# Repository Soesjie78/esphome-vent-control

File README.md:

🛠️ Smart Solar-Powered Ventilation Control (Matter / Home Assistant)
Convert your standard home ventilation grill or window register into a smart, energy-independent ventilation system! This 3D-printed project mounts a servo motor to your ventilation control and uses a super energy-efficient ESP32-C6 (FireBeetle 2) to operate automatically via Home Assistant (Matter/Thread or WiFi).

Thanks to advanced deep sleep optimization, this project can run entirely on a small LiPo battery topped up by a tiny solar panel!

## 🚀 Quick Installation

You can flash the firmware directly to your ESP8266 via your browser. Click the button below:

*Note: Please use a browser that supports WebSerial (Chrome, Edge, or Opera).*

✨ Features
Smart Home Integration: Works natively with Home Assistant and Matter via ESPHome.
Extreme Battery Life: The controller stays in ultra-low-power Deep Sleep, waking up every 20 minutes to sync and check for new commands. No massive battery needed!
Zero Latency "Queuing": Uses a Home Assistant Helper (input_select). You can change the desired position at any time in your dashboard; the device picks it up instantly the moment it wakes up.
Smart Memory: The servo only moves if the requested position has actually changed, saving tons of mechanical wear and battery power.
Solar Ready: Designed around the DFRobot FireBeetle 2 form factor for easy solar charging integration.

Further information can be foud at the Makerworld 3D model houding area: https://makerworld.com/en/models/2931636-smart-solar-vent-control-matter-home-assistant#profileId-3281956

## 🔌 Custom PCB (optional)

Prefer a single board instead of a FireBeetle + loose wiring? [`hardware/`](hardware/README.md) contains a
36 × 50 mm KiCad 7 design based on the ESP32-C6-MINI-1. It has a TP4056 solar/USB LiPo charger, a 3.3 V low-Iq LDO,
battery measurement, and a MOSFET that switches the servo supply completely off during deep sleep. Gerbers, BOM and CPL
for JLCPCB assembly are included. Use [`ventcontrol-pcb.yaml`](ventcontrol-pcb.yaml) as the firmware for this board.

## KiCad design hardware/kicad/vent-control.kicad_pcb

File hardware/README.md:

# Vent Control – eigen printplaat (ESP32-C6, zonnepaneel, LiPo, servo)

Een compacte printplaat (**36 × 50 mm, 2 lagen**) die de FireBeetle 2 ESP32-C6 + losse
bedrading vervangt. Alles wat je nu met losse onderdelen doet, zit op de print:
de Schottky-diode voor het zonnepaneel, en de MOSFET + weerstanden die de servo-voeding schakelen.

| Bovenkant | Onderkant (gespiegeld) |
|---|---|
|  |  |

Schema: [production/vent-control-schematic.pdf](production/vent-control-schematic.pdf)

## Wat zit erop

| Blok | Onderdelen | Opmerking |
|---|---|---|
| MCU | **ESP32-C6-MINI-1-N4** (U1) | Thread/Matter, WiFi 6, BLE. PCB-antenne aan de bovenrand; onder de antenne is een kopervrije zone van 5,6 mm. |
| USB-C | J1 + USBLC6-2SC6 (ESD) + 2× 5,1 kΩ CC | Flashen/loggen via de ingebouwde USB-Serial/JTAG (GPIO12/13) en opladen. |
| Zonnepaneel | J3 (JST-PH 2p) + **D2 B5819W Schottky** | USB (D1) en zonnepaneel (D2) zijn via diodes "ge-OR'd" naar de lader. 5–6 V paneel. |
| Lader | **TP4056** (U2), 500 mA (R3 = 2,4 kΩ) | Rode LED = laden, groene LED = vol. Max. ingangsspanning 8 V, dus een 6 V-paneel (Voc ≈ 7 V) is OK. |
| Batterij | J2 (JST-PH 2p), 1S LiPo | **Gebruik een cel mét beveiligingsprintje** (de TP4056 heeft geen onderspanningsbeveiliging). |
| 3,3 V | **XC6220B331MR** LDO (U3) | 1 A, ruststroom ±8 µA, lage dropout. |
| Batterijmeting | 1 MΩ / 1 MΩ + 100 nF → **GPIO0** | Zelfde als de FireBeetle (`multiply: 2.0`). Kost permanent ~2 µA. |
| Servo-voeding | **Q1 AO3401A** (P-FET) + **Q2 2N7002** + R12/R13/R14/C9 | **GPIO2** hoog = servo aan. In deep sleep is de servo volledig spanningsloos. R13/C9 geven een soft-start (~1 ms) tegen inschakelpieken; R14 houdt de servo uit tijdens reset/slaap. 47 µF + 100 nF buffer. |
| Servo | J4 (3-pin header, G-V-S) | Signaal op **GPIO1** via 1 kΩ. Servo (SG90/MG90 360°) draait direct op de accuspanning 3,0–4,2 V. |
| Knoppen/LED | RESET (EN), BOOT (GPIO9), status-LED (**GPIO18**) | GPIO8 heeft de verplichte pull-up voor het opstarten. |

### Pinnen samengevat

| Functie | GPIO | Verschil met FireBeetle-versie |
|---|---|---|
| Servo signaal | GPIO1 | zelfde |
| Batterijspanning (ADC, ×2) | GPIO0 | zelfde |
| Servo voeding aan/uit | GPIO2 | **nieuw** |
| Status-LED | GPIO18 | was GPIO15 ("Battery Measure Enable", dat was in feite de LED) |
| USB D-/D+ | GPIO12/13 | intern |

## Firmware

Gebruik [`../ventcontrol-pcb.yaml`](../ventcontrol-pcb.yaml) (gevalideerd met `esphome config`, ESPHome 2026.10.2).
De scripts zetten nu eerst de servo-voeding aan (GPIO2), bewegen de servo, stoppen,
en schakelen de voeding weer uit. Het apparaat gaat pas slapen als een servo-beweging klaar is.
De originele `ventcontrol.yaml` (FireBeetle) is ongewijzigd.

## Bestellen bij JLCPCB

1. **PCB**: upload `production/vent-control-gerbers.zip`. 2 lagen, 1,6 mm, standaard instellingen.
2. **PCB Assembly** (bovenkant): upload `production/bom-jlcpcb.csv` en `production/cpl-jlcpcb.csv`.
3. Controleer in de BOM-stap **elk onderdeel** (zie hieronder) en in de preview de **rotatie**
   van de onderdelen (vooral U1, U2, U3, U4, Q1, Q2, J1, de LEDs en dioden). JLCPCB's
   bibliotheek gebruikt soms een andere nul-rotatie dan KiCad; dat corrigeer je in de preview.
4. Zelf solderen (doorsteek): J2 + J3 (JST S2B-PH-K-S, liggend) en J4 (1×3 header).

### Let op: LCSC-nummers niet geverifieerd

Vanuit deze omgeving kon ik de catalogus van LCSC/JLCPCB niet bereiken. De LCSC-nummers in de BOM
zijn uit mijn kennis ingevuld en **moeten gecontroleerd worden**. Voor deze onderdelen moet je zelf een
nummer kiezen (zoek op MPN):

| Ref | Onderdeel |
|---|---|
| U1 | ESP32-C6-MINI-1-N4 (Espressif) |
| U3 | XC6220B331MR-G (Torex), of een pin-compatibele low-Iq LDO (SOT-23-5: VIN, GND, CE, NC, VOUT) |
| C10 | 47 µF 1206 ≥ 6,3 V X5R |
| R3 | 2,4 kΩ 0603 (bepaalt de laadstroom: I ≈ 1200 / R3) |

## ⚠️ Belangrijk vóór gebruik

* **Polariteit JST-batterij!** JST-PH-accu's hebben géén vaste kleurconventie. Op de print is
  **pin 1 = + (vierkante pad, "+" in de silkscreen)**. Controleer dit met een multimeter vóór je inplugt.
  Een omgekeerde accu beschadigt de lader en de LDO (er zit geen ompoolbeveiliging op).
* **Laadstroom 500 mA**: geschikt voor accu's vanaf ±500 mAh. Bij een kleinere accu R3 verhogen
  (bijv. 4,7 kΩ ≈ 250 mA).
* De TP4056 heeft geen MPPT. Voor een klein paneel (≤ 2 W) werkt dat prima.
* De ESP32 hangt direct aan de accu (geen "load sharing"). Omdat het apparaat bijna altijd slaapt,
  is dat geen probleem voor het laadeinde.
* Houd metaal en batterij weg van de antennezone (bovenste 5,6 mm) in de behuizing.
* **Verwacht slaapverbruik (geschat, niet gemeten)**: ESP32-C6 deep sleep (~7 µA), LDO (~8 µA),
  spanningsdeler (~2 µA), lader/lekstroom (enkele µA). Dat is totaal ordegrootte 20 µA.
  De servo trekt niets meer.

## Hoe dit ontwerp gemaakt en gecontroleerd is

Alles wordt gegenereerd uit één bestand, [`generator/design.py`](generator/design.py) (onderdelen + netten):

```
generator/build.sh      # draait alle stappen hieronder (KiCad 7 nodig)
  gen_lib.py            # projectsymbolen (ESP32-C6-MINI-1, TP4056) + module-footprint
  gen_sch.py            # schema (kicad/vent-control.kicad_sch)
  check_sch.py          # exporteert de netlist met kicad-cli en vergelijkt met design.py
  route.py              # plaatsing (gen_pcb.py) + eigen A*-router (2 lagen, 0/45/90°)
  finish_pcb.py         # GND-vlakken op beide lagen + KiCad DRC
  export.py             # Gerbers, boorbestanden, BOM, CPL, PDF's
```

Uitgevoerde controles:

* **Schema ↔ ontwerp**: de door KiCad geëxporteerde netlist komt exact overeen
  (27 netten, 47 componenten; geen enkelvoudige netten, voedingsingangen gevoed).
  Let op: `kicad-cli` van KiCad 7 heeft nog geen ERC, dus dit is een eigen controle i.p.v. KiCad's ERC.
  Open het schema in KiCad en draai ERC voor een tweede mening.
* **PCB ↔ ontwerp**: alle 145 pin-net-toewijzingen op de PCB gecontroleerd.
* **KiCad DRC: 0 fouten, 0 onverbonden** ([drc-report.txt](production/drc-report.txt)).
  De overgebleven meldingen zijn waarschuwingen: silkscreen die over pads/rand valt (wordt door de
  fabrikant weggeknipt), en "lib_footprint_issues" omdat de footprint-bibliotheek in headless modus
  niet geladen is.
* Regels: spoor ≥ 0,2 mm (signaal 0,25, voeding 0,4), clearance 0,2 mm, via 0,6/0,3 mm. Dat valt ruim binnen
  de standaard JLCPCB-specificaties.

De footprint van de ESP32-C6-MINI-1 is omgezet uit de officiële KiCad-bibliotheek
(`lib/upstream/`, KiCad 10-formaat, CC-BY-SA 4.0 met uitzondering) naar KiCad 7-formaat.
De padgeometrie is 1-op-1 overgenomen.

**Dit ontwerp is niet fysiek getest.** Bestel eerst een kleine serie (5 stuks) en meet bij de
eerste print de 3,3 V, de laadfunctie en het slaapverbruik voordat je er meer maakt.

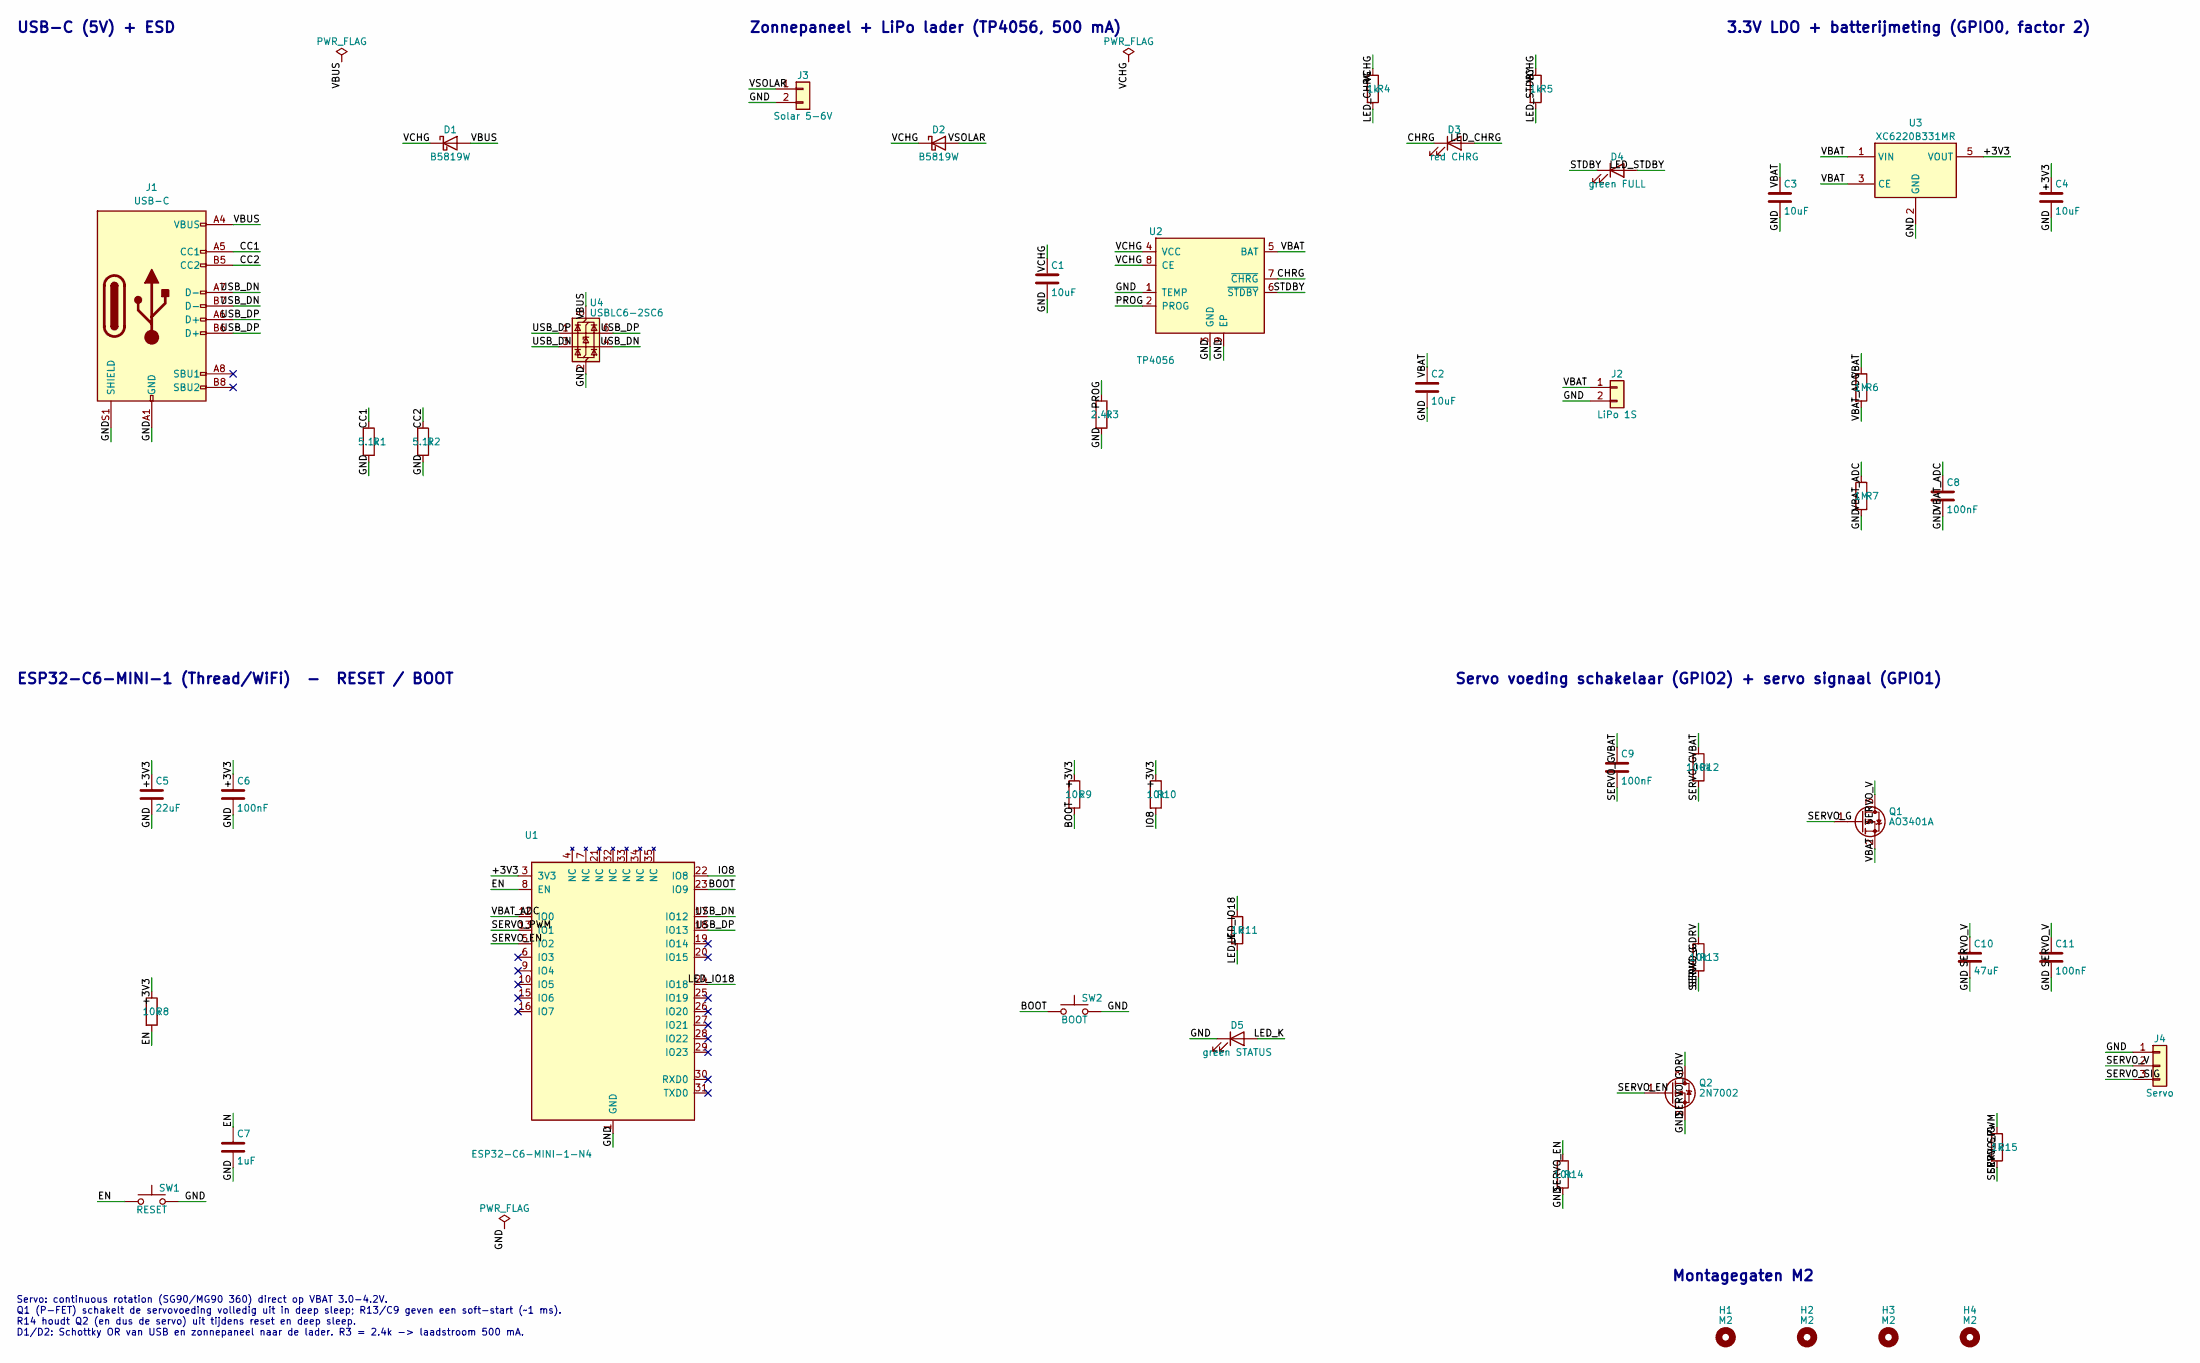
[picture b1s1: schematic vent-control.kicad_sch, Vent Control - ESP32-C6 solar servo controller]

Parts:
C1, C2, C3, C4: 10uF; C_0805_2012Metric; MPN CL21A106KAYNNNE; LCSC C15850
C5: 22uF; C_0805_2012Metric; MPN CL21A226MAQNNNE; LCSC C45783
C6, C8, C9, C11: 100nF; C_0603_1608Metric; MPN CL10B104KB8NNNC; LCSC C14663
C7: 1uF; C_0603_1608Metric; MPN CL10A105KB8NNNC; LCSC C15849
C10: 47uF; C_1206_3216Metric; MPN CL31A476MQHNNNE
D1, D2: B5819W; D_SOD-123; MPN B5819W; LCSC C8598
D3: red CHRG; LED_0603_1608Metric; MPN KT-0603R; LCSC C2286
D4: green FULL; LED_0603_1608Metric; MPN 19-217/GHC-YR1S2/3T; LCSC C72043
D5: green STATUS; LED_0603_1608Metric; MPN 19-217/GHC-YR1S2/3T; LCSC C72043
H1, H2, H3, H4: M2; MountingHole_2.2mm_M2
J1: USB-C; USB_C_Receptacle_HRO_TYPE-C-31-M-12; MPN HRO TYPE-C-31-M-12; LCSC C165948
J2: LiPo 1S; JST_PH_S2B-PH-K_1x02_P2.00mm_Horizontal; MPN JST S2B-PH-K-S
J3: Solar 5-6V; JST_PH_S2B-PH-K_1x02_P2.00mm_Horizontal; MPN JST S2B-PH-K-S
J4: Servo; PinHeader_1x03_P2.54mm_Vertical; MPN 2.54mm pin header 1x3
Q1: AO3401A; SOT-23; MPN AO3401A; LCSC C15127
Q2: 2N7002; SOT-23; MPN 2N7002; LCSC C8545
R1, R2: 5.1k; R_0603_1608Metric; MPN 0603WAF5101T5E; LCSC C23186
R3: 2.4k; R_0603_1608Metric; MPN 0603WAF2401T5E
R4, R5, R11, R15: 1k; R_0603_1608Metric; MPN 0603WAF1001T5E; LCSC C21190
R6, R7: 1M; R_0603_1608Metric; MPN 0603WAF1004T5E; LCSC C22935
R8, R9, R10, R13, R14: 10k; R_0603_1608Metric; MPN 0603WAF1002T5E; LCSC C25804
R12: 100k; R_0603_1608Metric; MPN 0603WAF1003T5E; LCSC C25803
SW1: RESET; SW_Push_1P1T_XKB_TS-1187A; MPN TS-1187A-B-A-B; LCSC C318884
SW2: BOOT; SW_Push_1P1T_XKB_TS-1187A; MPN TS-1187A-B-A-B; LCSC C318884
U1: ESP32-C6-MINI-1-N4; ESP32-C6-MINI-1; MPN ESP32-C6-MINI-1-N4
U2: TP4056; SOIC-8-1EP_3.9x4.9mm_P1.27mm_EP2.41x3.3mm; MPN TP4056-42-ESOP8; LCSC C16581
U3: XC6220B331MR; SOT-23-5; MPN XC6220B331MR-G
U4: USBLC6-2SC6; SOT-23-6; MPN USBLC6-2SC6; LCSC C7519

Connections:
+3V3: C4.1, C5.1, C6.1, R8.1, R9.1, R10.1, U1.3 (3V3), U3.5 (VOUT)
BOOT: R9.2, SW2.1, U1.23 (IO9)
CC1: J1.A5 (CC1), R1.1
CC2: J1.B5 (CC2), R2.1
CHRG: D3.1 (K), U2.7 (~CHRG)
EN: C7.1, R8.2, SW1.1, U1.8 (EN)
GND: C1.2, C2.2, C3.2, C4.2, C5.2, C6.2, C7.2, C8.2, C10.2, C11.2, D5.1 (K), J1.A1 (GND), J1.A12 (GND), J1.B1 (GND), J1.B12 (GND), J1.S1 (SHIELD), J2.2, J3.2, J4.1, Q2.2 (S), R1.2, R2.2, R3.2, R7.2, R14.2, SW1.2, SW2.2, U1.1 (GND), U1.2 (GND), U1.11 (GND), U1.14 (GND), U1.36 (GND), U1.37 (GND), U1.38 (GND), U1.39 (GND), U1.40 (GND), U1.41 (GND), U1.42 (GND), U1.43 (GND), U1.44 (GND), U1.45 (GND), U1.46 (GND), U1.47 (GND), U1.48 (GND), U1.49 (GND), U1.50 (GND), U1.51 (GND), U1.52 (GND), U1.53 (GND), U2.1 (TEMP), U2.3 (GND), U2.9 (EP), U3.2 (GND), U4.2 (GND)
IO8: R10.2, U1.22 (IO8)
LED_CHRG: D3.2 (A), R4.2
LED_IO18: R11.1, U1.24 (IO18)
LED_K: D5.2 (A), R11.2
LED_STDBY: D4.2 (A), R5.2
PROG: R3.1, U2.2 (PROG)
SERVO_EN: Q2.1 (G), R14.1, U1.5 (IO2)
SERVO_G: C9.2, Q1.1 (G), R12.2, R13.2
SERVO_GDRV: Q2.3 (D), R13.1
SERVO_PWM: R15.1, U1.13 (IO1)
SERVO_SIG: J4.3, R15.2
SERVO_V: C10.1, C11.1, J4.2, Q1.3 (D)
STDBY: D4.1 (K), U2.6 (~STDBY)
USB_DN: J1.A7 (D-), J1.B7 (D-), U1.17 (IO12), U4.3 (I/O2), U4.4 (I/O2)
USB_DP: J1.A6 (D+), J1.B6 (D+), U1.18 (IO13), U4.1 (I/O1), U4.6 (I/O1)
VBAT: C2.1, C3.1, C9.1, J2.1, Q1.2 (S), R6.1, R12.1, U2.5 (BAT), U3.1 (VIN), U3.3 (CE)
VBAT_ADC: C8.1, R6.2, R7.1, U1.12 (IO0)
VBUS: D1.2 (A), J1.A4 (VBUS), J1.A9 (VBUS), J1.B4 (VBUS), J1.B9 (VBUS), U4.5 (VBUS)
VCHG: C1.1, D1.1 (K), D2.1 (K), R4.1, R5.1, U2.4 (VCC), U2.8 (CE)
VSOLAR: D2.2 (A), J3.1

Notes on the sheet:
USB-C (5V) + ESD
Zonnepaneel + LiPo lader (TP4056, 500 mA)
3.3V LDO + batterijmeting (GPIO0, factor 2)
ESP32-C6-MINI-1 (Thread/WiFi) - RESET / BOOT
Servo voeding schakelaar (GPIO2) + servo signaal (GPIO1)
Montagegaten M2
Servo: continuous rotation (SG90/MG90 360) direct op VBAT 3.0-4.2V. Q1 (P-FET) schakelt de servovoeding volledig uit in deep sleep; R13/C9 geven een soft-start (~1 ms). R14 houdt Q2 (en dus de servo) uit tijdens reset en deep sleep. D1/D2: Schottky OR van USB en zonnepaneel naar de lader. R3 = 2.4k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

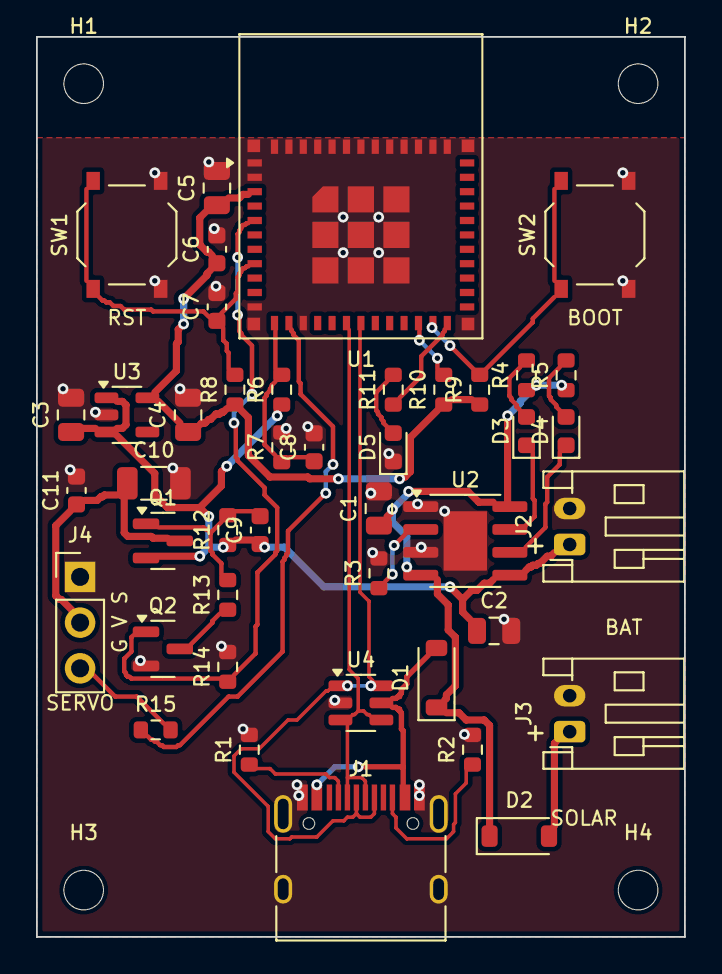
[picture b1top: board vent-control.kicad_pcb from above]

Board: 2 copper layers, 36.0 x 50.0 mm, 47 parts (0 on the bottom side), 27 nets.

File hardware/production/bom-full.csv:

Qty,Designator,Value,MPN,LCSC (verify),Footprint,Assembly
4,"C1,C2,C3,C4",10uF,CL21A106KAYNNNE,C15850,C_0805_2012Metric,JLCPCB SMT
1,C5,22uF,CL21A226MAQNNNE,C45783,C_0805_2012Metric,JLCPCB SMT
4,"C6,C8,C9,C11",100nF,CL10B104KB8NNNC,C14663,C_0603_1608Metric,JLCPCB SMT
1,C7,1uF,CL10A105KB8NNNC,C15849,C_0603_1608Metric,JLCPCB SMT
1,C10,47uF,CL31A476MQHNNNE,,C_1206_3216Metric,JLCPCB SMT
2,"D1,D2",B5819W,B5819W,C8598,D_SOD-123,JLCPCB SMT
1,D3,red CHRG,KT-0603R,C2286,LED_0603_1608Metric,JLCPCB SMT
1,D4,green FULL,19-217/GHC-YR1S2/3T,C72043,LED_0603_1608Metric,JLCPCB SMT
1,D5,green STATUS,19-217/GHC-YR1S2/3T,C72043,LED_0603_1608Metric,JLCPCB SMT
1,J1,USB-C,HRO TYPE-C-31-M-12,C165948,USB_C_Receptacle_HRO_TYPE-C-31-M-12,JLCPCB SMT
1,J2,LiPo 1S,JST S2B-PH-K-S,,JST_PH_S2B-PH-K_1x02_P2.00mm_Horizontal,hand solder
1,J3,Solar 5-6V,JST S2B-PH-K-S,,JST_PH_S2B-PH-K_1x02_P2.00mm_Horizontal,hand solder
1,J4,Servo,2.54mm pin header 1x3,,PinHeader_1x03_P2.54mm_Vertical,hand solder
1,Q1,AO3401A,AO3401A,C15127,SOT-23,JLCPCB SMT
1,Q2,2N7002,2N7002,C8545,SOT-23,JLCPCB SMT
2,"R1,R2",5.1k,0603WAF5101T5E,C23186,R_0603_1608Metric,JLCPCB SMT
1,R3,2.4k,0603WAF2401T5E,,R_0603_1608Metric,JLCPCB SMT
4,"R4,R5,R11,R15",1k,0603WAF1001T5E,C21190,R_0603_1608Metric,JLCPCB SMT
2,"R6,R7",1M,0603WAF1004T5E,C22935,R_0603_1608Metric,JLCPCB SMT
5,"R8,R9,R10,R13,R14",10k,0603WAF1002T5E,C25804,R_0603_1608Metric,JLCPCB SMT
1,R12,100k,0603WAF1003T5E,C25803,R_0603_1608Metric,JLCPCB SMT
1,SW1,RESET,TS-1187A-B-A-B,C318884,SW_Push_1P1T_XKB_TS-1187A,JLCPCB SMT
1,SW2,BOOT,TS-1187A-B-A-B,C318884,SW_Push_1P1T_XKB_TS-1187A,JLCPCB SMT
1,U1,ESP32-C6-MINI-1-N4,ESP32-C6-MINI-1-N4,,ESP32-C6-MINI-1,JLCPCB SMT
1,U2,TP4056,TP4056-42-ESOP8,C16581,SOIC-8-1EP_3.9x4.9mm_P1.27mm_EP2.41x3.3mm,JLCPCB SMT
1,U3,XC6220B331MR,XC6220B331MR-G,,SOT-23-5,JLCPCB SMT
1,U4,USBLC6-2SC6,USBLC6-2SC6,C7519,SOT-23-6,JLCPCB SMT

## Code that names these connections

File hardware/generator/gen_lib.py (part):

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        pin(4, "VCC", "power_in", -12.7, 5.08, 0),
        pin(8, "CE", "input", -12.7, 2.54, 0),
        pin(1, "TEMP", "input", -12.7, -2.54, 0),
        pin(2, "PROG", "passive", -12.7, -5.08, 0),
        pin(5, "BAT", "power_out", 12.7, 5.08, 180),
        pin(7, "~{CHRG}", "open_collector", 12.7, 0, 180),
        pin(6, "~{STDBY}", "open_collector", 12.7, -2.54, 180),
        pin(3, "GND", "power_in", 0, -12.7, 90),
        pin(9, "EP", "passive", 2.54, -12.7, 90),
    ]
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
